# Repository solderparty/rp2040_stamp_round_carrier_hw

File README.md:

# The RP2040 Stamp Round Carrier

The RP2040 Stamp Round Carrier is a reference design for the RP2040 Stamp as well as a full-fledged round RP2040 dev board.
The HW files for the Stamp can be found here: https://github.com/solderparty/rp2040_stamp_hw

The Carrier comes with a combo 3-in-1 SMD/TH/FlexyPin Stamp footprint, you can solder the Stamp directly to the Carrier, use 2mm pin headers + sockets to be able to plug it in and out, or use FlexyPins to pop the Stamp in and out of the Carrier would soldering the Stamp. This way the Carrier also acts as a great Stamp flashing and testing jig.

On top of all the functionality of the Stamp, the Carrier also adds:
* A ring of 16 Neopixels
* Combo 3-in-1 Stamp footprint (SMD/TH/FlexyPin)
* Sewing (conductive thread) and alligator clip-friendly pads
* An on/off switch
* 3.7/4.2V LiPo connector
* USR LED
* Power (3.3V) LED
* Two user buttons
* USB Type-C connector

# Links

For more information visit https://rp2040-stamp.solder.party/

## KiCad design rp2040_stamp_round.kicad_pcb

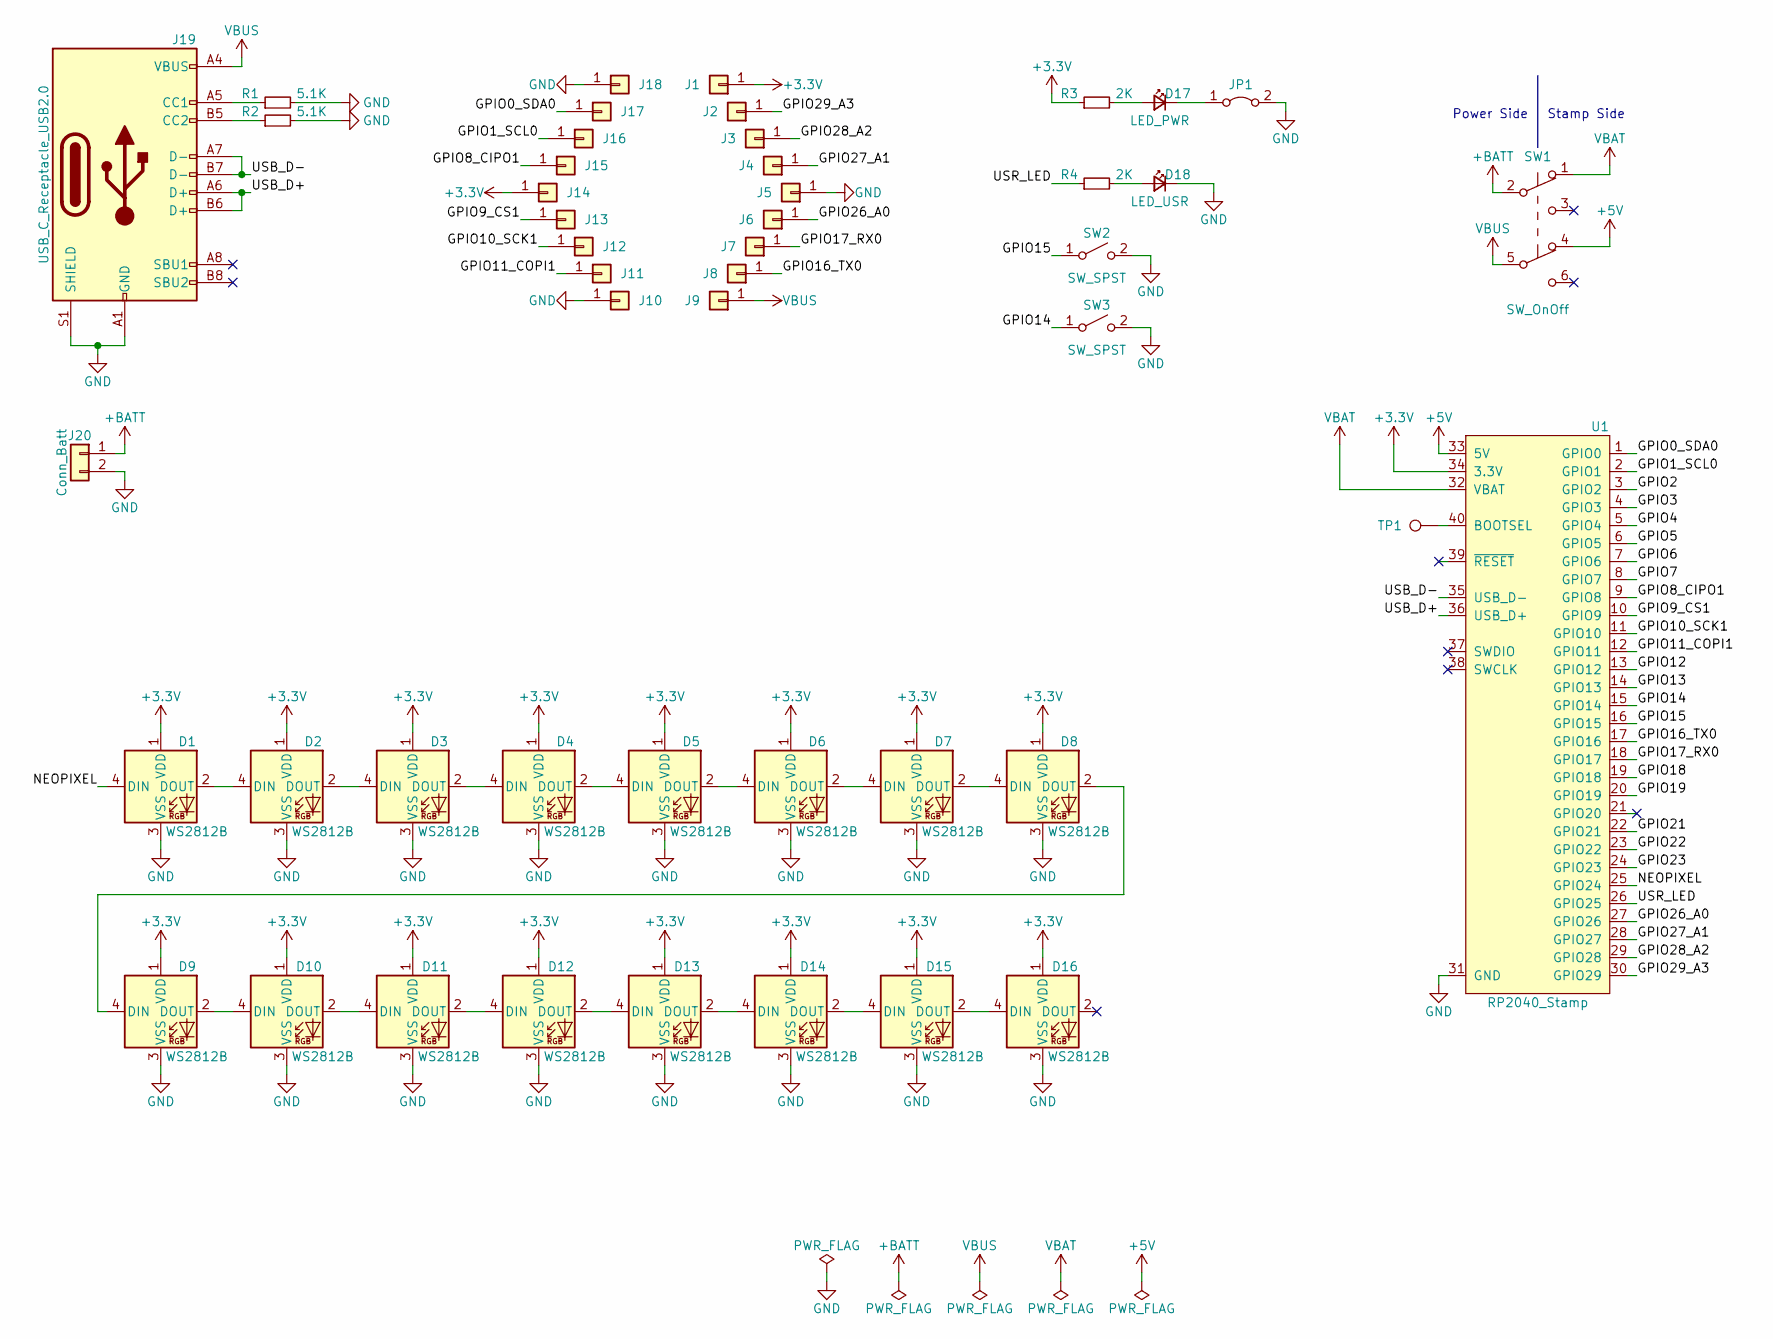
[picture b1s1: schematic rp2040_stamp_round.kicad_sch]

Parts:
D1, D2, D3, D4, D5, D6, D7, D8, D9, D10, D11, D12, D13, D14, D15, D16: WS2812B; LED_WS2812B_PLCC4_3.5x3.5mm_P1.78mm; LCSC C527089
D17: LED_PWR; LED_0603_1608Metric
D18: LED_USR; LED_0603_1608Metric
J1, J2, J3, J4, J5, J6, J7, J8, J9, J10, J11, J12, J13, J14, J15, J16, J17, J18: Conn_01x01; MountingHole_3.2mm_M3_Pad_Polygon
J19: USB_C_Receptacle_USB2.0; USB_C_Receptacle_XKB_U262-16XN-4BVC11; LCSC C319148
J20: Conn_Batt; JST_PH_S2B-PH-SM4-TB_1x02-1MP_P2.00mm_Horizontal; LCSC C47647
JP1: Jumper_PWR; SolderJumper-2_P1.3mm_Bridged_RoundedPad1.0x1.5mm
R1, R2: 5.1K; R_0603_1608Metric
R3, R4: 2K; R_0603_1608Metric
SW1: SW_OnOff; SW_DPDT_CK_JS202011JCQN; LCSC C221665
SW2, SW3: SW_SPST; SW_SPST_B3U-1000P-B; LCSC C561514
TP1: TP_BOOTSEL; TestPoint_Pad_D2.0mm
U1: RP2040_Stamp; RP2040_Stamp_Springs

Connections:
+3V3: D1.1 (VDD), D2.1 (VDD), D3.1 (VDD), D4.1 (VDD), D5.1 (VDD), D6.1 (VDD), D7.1 (VDD), D8.1 (VDD), D9.1 (VDD), D10.1 (VDD), D11.1 (VDD), D12.1 (VDD), D13.1 (VDD), D14.1 (VDD), D15.1 (VDD), D16.1 (VDD), J1.1, J14.1, R3.1, U1.34 (3.3V)
+5V: SW1.4 (A), U1.33 (5V)
+BATT: J20.1, SW1.2 (B)
/GPIO0_SDA0: J17.1, U1.1 (GPIO0)
/GPIO1_SCL0: J16.1, U1.2 (GPIO1)
/GPIO2: U1.3 (GPIO2)
/GPIO3: U1.4 (GPIO3)
/GPIO4: U1.5 (GPIO4)
/GPIO5: U1.6 (GPIO5)
/GPIO6: U1.7 (GPIO6)
/GPIO7: U1.8 (GPIO7)
/GPIO8_CIPO1: J15.1, U1.9 (GPIO8)
/GPIO9_CS1: J13.1, U1.10 (GPIO9)
/GPIO10_SCK1: J12.1, U1.11 (GPIO10)
/GPIO11_COPI1: J11.1, U1.12 (GPIO11)
/GPIO12: U1.13 (GPIO12)
/GPIO13: U1.14 (GPIO13)
/GPIO14: SW3.1 (A), U1.15 (GPIO14)
/GPIO15: SW2.1 (A), U1.16 (GPIO15)
/GPIO16_TX0: J8.1, U1.17 (GPIO16)
/GPIO17_RX0: J7.1, U1.18 (GPIO17)
/GPIO18: U1.19 (GPIO18)
/GPIO19: U1.20 (GPIO19)
/GPIO21: U1.22 (GPIO21)
/GPIO22: U1.23 (GPIO22)
/GPIO23: U1.24 (GPIO23)
/GPIO26_A0: J6.1, U1.27 (GPIO26)
/GPIO27_A1: J4.1, U1.28 (GPIO27)
/GPIO28_A2: J3.1, U1.29 (GPIO28)
/GPIO29_A3: J2.1, U1.30 (GPIO29)
/NEOPIXEL: D1.4 (DIN), U1.25 (GPIO24)
/USB_D+: J19.A6 (D+), J19.B6 (D+), U1.36 (USB_D+)
/USB_D-: J19.A7 (D-), J19.B7 (D-), U1.35 (USB_D-)
/USR_LED: R4.1, U1.26 (GPIO25)
GND: D1.3 (VSS), D2.3 (VSS), D3.3 (VSS), D4.3 (VSS), D5.3 (VSS), D6.3 (VSS), D7.3 (VSS), D8.3 (VSS), D9.3 (VSS), D10.3 (VSS), D11.3 (VSS), D12.3 (VSS), D13.3 (VSS), D14.3 (VSS), D15.3 (VSS), D16.3 (VSS), D18.1 (K), J5.1, J10.1, J18.1, J19.A1 (GND), J19.A12 (GND), J19.B1 (GND), J19.B12 (GND), J19.S1 (SHIELD), J20.2, JP1.2 (B), R1.2, R2.2, SW2.2 (B), SW3.2 (B), U1.31 (GND)
unnamed: D1.2 (DOUT), D2.4 (DIN)
unnamed: D2.2 (DOUT), D3.4 (DIN)
unnamed: D3.2 (DOUT), D4.4 (DIN)
unnamed: D4.2 (DOUT), D5.4 (DIN)
unnamed: D5.2 (DOUT), D6.4 (DIN)
unnamed: D6.2 (DOUT), D7.4 (DIN)
unnamed: D7.2 (DOUT), D8.4 (DIN)
unnamed: D8.2 (DOUT), D9.4 (DIN)
unnamed: D9.2 (DOUT), D10.4 (DIN)
unnamed: D10.2 (DOUT), D11.4 (DIN)
unnamed: D11.2 (DOUT), D12.4 (DIN)
unnamed: D12.2 (DOUT), D13.4 (DIN)
unnamed: D13.2 (DOUT), D14.4 (DIN)
unnamed: D14.2 (DOUT), D15.4 (DIN)
unnamed: D15.2 (DOUT), D16.4 (DIN)
unnamed: D17.2 (A), R3.2
unnamed: D17.1 (K), JP1.1 (A)
unnamed: D18.2 (A), R4.2
unnamed: J19.A5 (CC1), R1.1
unnamed: J19.B5 (CC2), R2.1
unnamed: TP1.1, U1.40 (BOOTSEL)
VBAT: SW1.1 (A), U1.32 (VBAT)
VBUS: J9.1, J19.A4 (VBUS), J19.A9 (VBUS), J19.B4 (VBUS), J19.B9 (VBUS), SW1.5 (B)

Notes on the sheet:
Stamp Side
Power Side

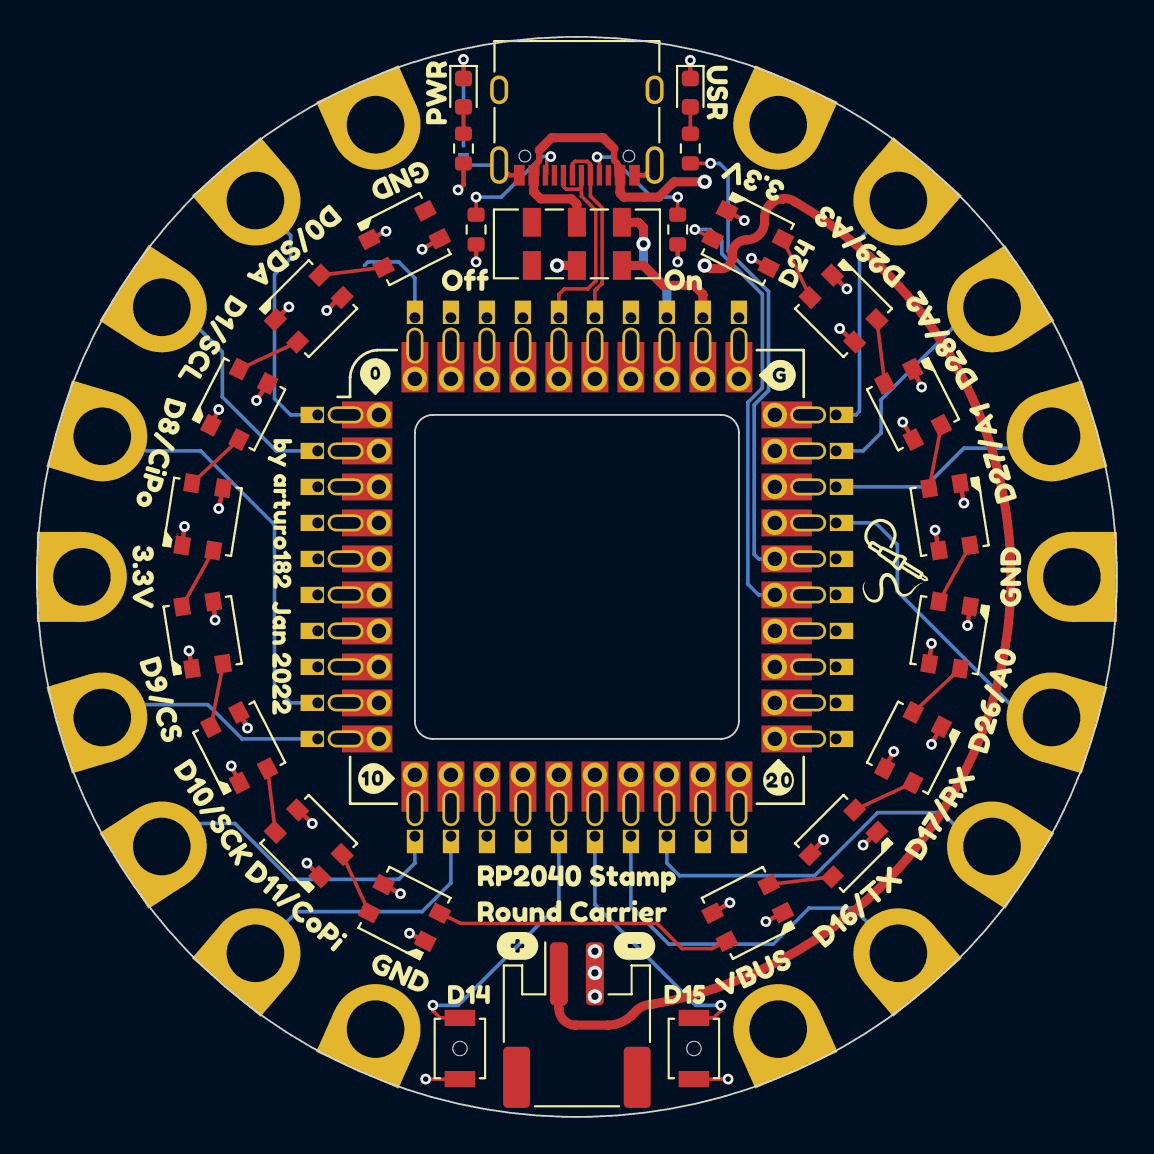
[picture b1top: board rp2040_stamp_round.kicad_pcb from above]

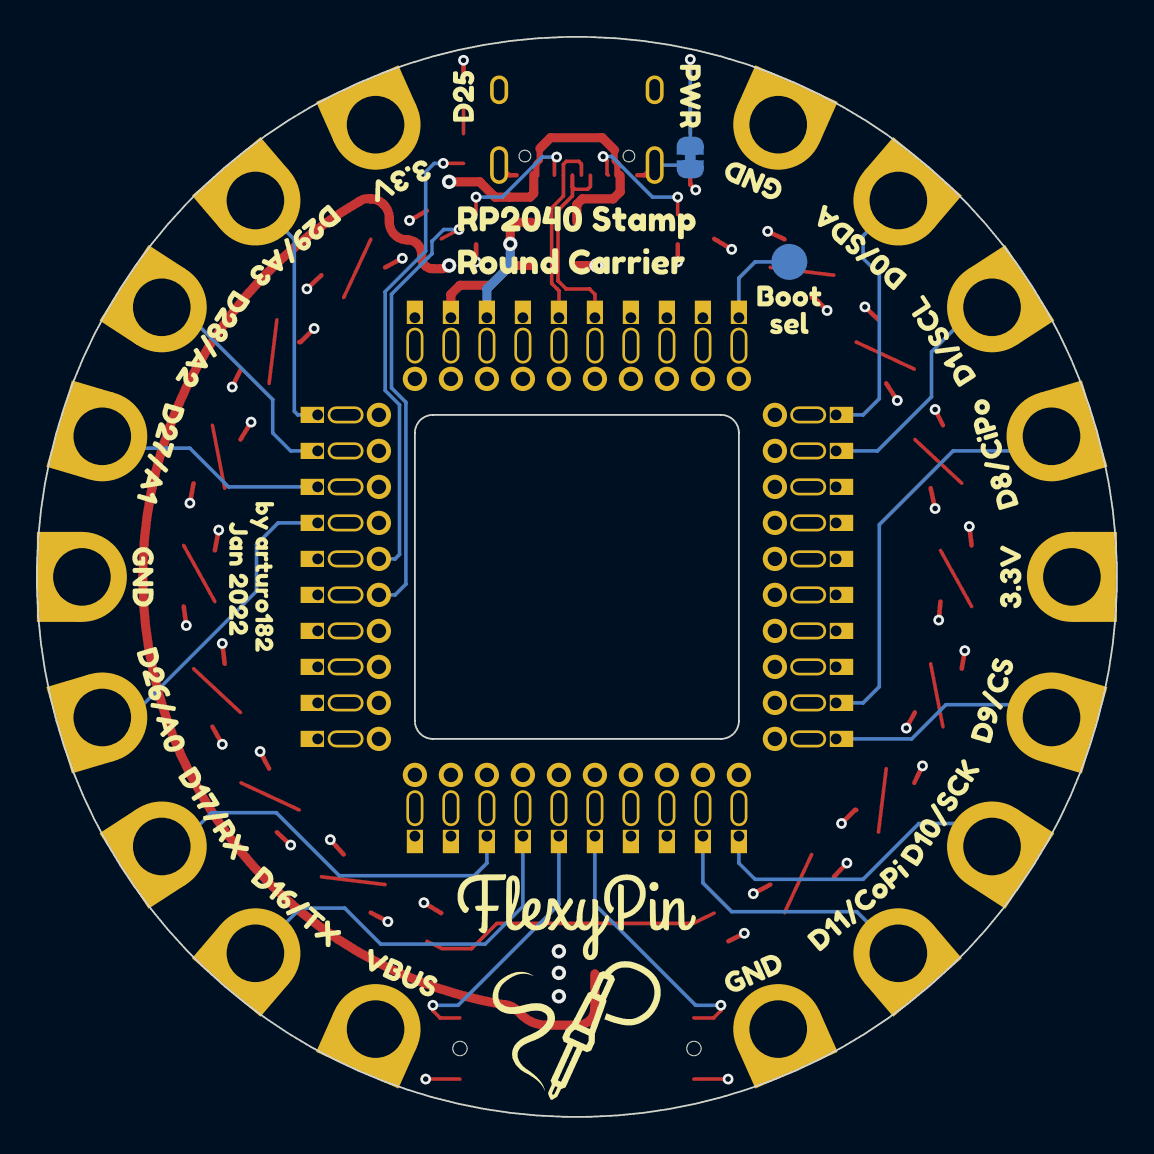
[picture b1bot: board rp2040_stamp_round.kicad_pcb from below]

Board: 4 copper layers, 60.0 x 60.0 mm, 103 parts (27 on the bottom side), 45 nets.

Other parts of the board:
kibuzzard-61B7CACE, kibuzzard-61B7CACE#2: G***; kibuzzard-61B7CACE
kibuzzard-61B7CB2A, kibuzzard-61B7CB2A#2, kibuzzard-61B7CB2A#3, kibuzzard-61B7CB2A#4: G***; kibuzzard-61B7CB2A
kibuzzard-61B7CB91, kibuzzard-61B7CB91#2, kibuzzard-61B7CB91#3, kibuzzard-61B7CB91#4, kibuzzard-61B7CB91#5, kibuzzard-61B7CB91#6: G***; kibuzzard-61B7CB91
kibuzzard-61B7F7A6, kibuzzard-61B7F7A6#2: G***; kibuzzard-61B7F7A6
kibuzzard-61B7F7BF, kibuzzard-61B7F7BF#2: G***; kibuzzard-61B7F7BF
kibuzzard-61B7F7D5, kibuzzard-61B7F7D5#2: G***; kibuzzard-61B7F7D5
kibuzzard-61B7F7FD, kibuzzard-61B7F7FD#2: G***; kibuzzard-61B7F7FD
kibuzzard-61B7F819, kibuzzard-61B7F819#2: G***; kibuzzard-61B7F819
kibuzzard-61B7FA9B, kibuzzard-61B7FA9B#2: G***; kibuzzard-61B7FA9B
kibuzzard-61B7FAB5, kibuzzard-61B7FAB5#2: G***; kibuzzard-61B7FAB5
kibuzzard-61B7FADB, kibuzzard-61B7FADB#2: G***; kibuzzard-61B7FADB
kibuzzard-61B7FB04, kibuzzard-61B7FB04#2: G***; kibuzzard-61B7FB04
kibuzzard-61B7FB19, kibuzzard-61B7FB19#2: G***; kibuzzard-61B7FB19
kibuzzard-61B7FB48, kibuzzard-61B7FB48#2: G***; kibuzzard-61B7FB48
kibuzzard-61B7FFB7: G***; kibuzzard-61B7FFB7
kibuzzard-61B788A5, kibuzzard-61B788A5#2: G***; kibuzzard-61B788A5
kibuzzard-61B789B2: G***; kibuzzard-61B789B2
kibuzzard-61B804DF: G***; kibuzzard-61B804DF
kibuzzard-61B804E7: G***; kibuzzard-61B804E7
kibuzzard-61B8067D: G***; kibuzzard-61B8067D
kibuzzard-61B8084E: G***; kibuzzard-61B8084E
kibuzzard-61B78991: G***; kibuzzard-61B78991
kibuzzard-61B80856: G***; kibuzzard-61B80856
kibuzzard-61BA2B21, kibuzzard-61BA2B21#2: G***; kibuzzard-61BA2B21
kibuzzard-61BA4CE2: G***; kibuzzard-61BA4CE2
kibuzzard-61DD95B3: G***; kibuzzard-61DD95B3
kibuzzard-61DD95E6: G***; kibuzzard-61DD95E6
kibuzzard-61DD95F0: G***; kibuzzard-61DD95F0
kibuzzard-61DD9534, kibuzzard-61DD9534#2: G***; kibuzzard-61DD9534
kibuzzard-61DD9594: G***; kibuzzard-61DD9594
kibuzzard-61E0313F: G***; kibuzzard-61E0313F
kibuzzard-61E03091: G***; kibuzzard-61E03091

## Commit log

2021-12-15 Rev 1
2022-05-07 Production rev release
2022-06-21 Fix stamp footprint submodule
